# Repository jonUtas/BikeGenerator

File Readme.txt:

Pedal generator for open day. 

Based on Bafang bike motor.

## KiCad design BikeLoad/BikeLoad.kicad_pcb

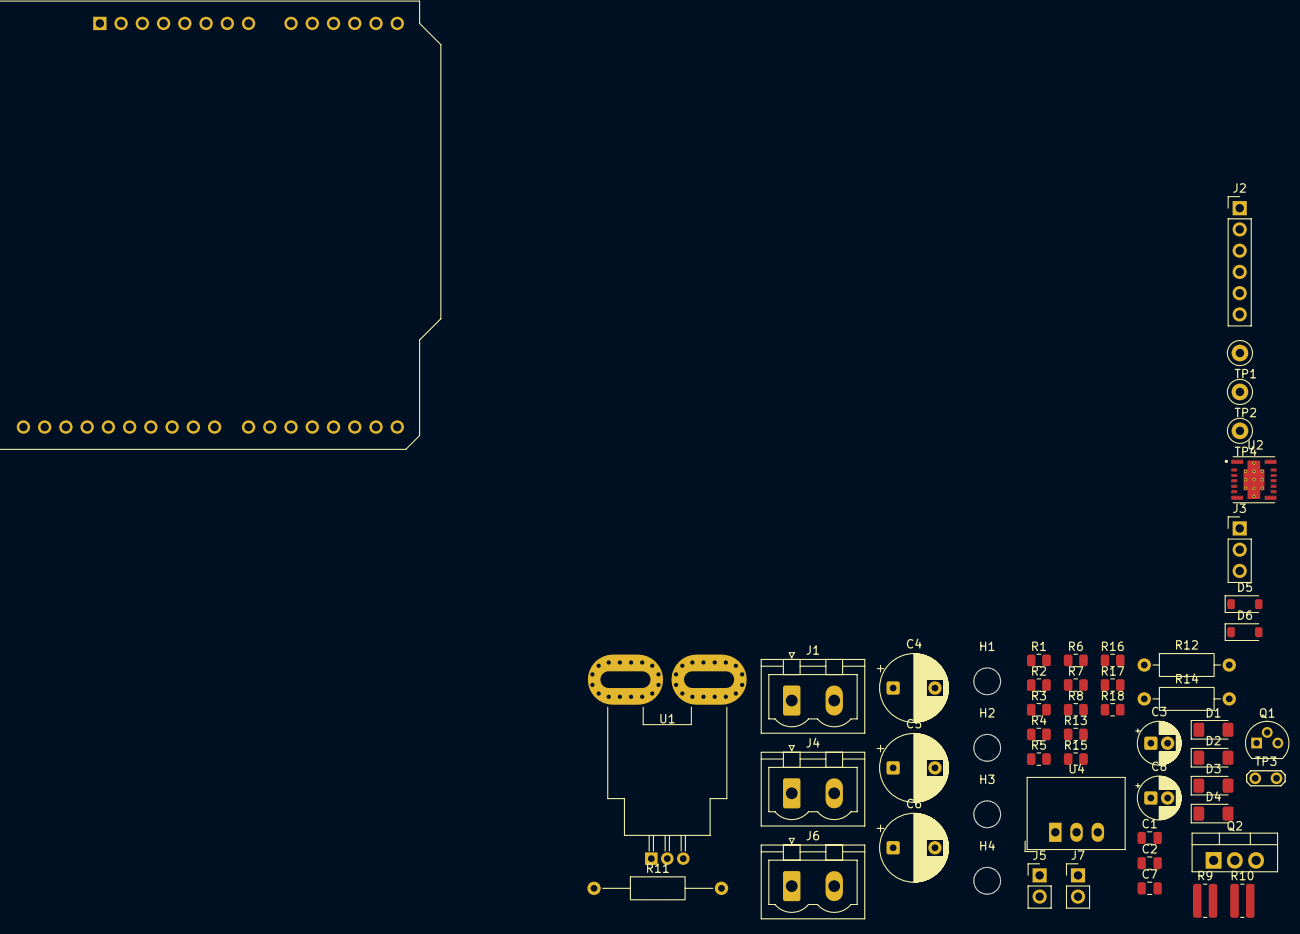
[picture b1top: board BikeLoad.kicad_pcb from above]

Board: 2 copper layers, 53 parts (0 on the bottom side), 26 nets, no tracks yet.

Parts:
A1: Arduino_UNO_R3
C1, C2, C7: C; C_0805_2012Metric
C3: C_Polarized; CP_Radial_D5.0mm_P2.00mm
C4, C5, C6: 1; CP_Radial_D8.0mm_P5.00mm
C8: 10u; CP_Radial_D5.0mm_P2.00mm
D1: BZV55B51; D_MiniMELF
D2, D3, D4: BZV55B4V3; D_MiniMELF
D5, D6: D; D_SOD-123
H1, H2, H3, H4: MountingHole; MountingHole_3.2mm_M3
J1: DC Input; PhoenixContact_MSTBVA_2,5_2-G-5,08_1x02_P5.08mm_Vertical
J2: Hall Input; PinHeader_1x06_P2.54mm_Vertical
J3: Pot Input; PinHeader_1x03_P2.54mm_Vertical
J4: Load; PhoenixContact_MSTBVA_2,5_2-G-5,08_1x02_P5.08mm_Vertical
J5: Temp sensor; PinHeader_1x02_P2.54mm_Vertical
J6: DC out; PhoenixContact_MSTBVA_2,5_2-G-5,08_1x02_P5.08mm_Vertical
J7: LoadControl; PinHeader_1x02_P2.54mm_Vertical
Q1: BC556; TO-92
Q2: PNP; TO-220-3_Vertical
R1, R5, R6, R15, R16, R17, R18: R; R_0805_2012Metric
R2, R3, R4, R7, R13: 10k; R_0805_2012Metric
R8: 1k; R_0805_2012Metric
R9, R10: R; R_0815_2038Metric
R11: R; R_Axial_DIN0207_L6.3mm_D2.5mm_P15.24mm_Horizontal
R12: R; R_Axial_DIN0207_L6.3mm_D2.5mm_P10.16mm_Horizontal
R14: 10k; R_Axial_DIN0207_L6.3mm_D2.5mm_P10.16mm_Horizontal
TP1, TP2, TP4: TestPoint; TestPoint_Loop_D1.80mm_Drill1.0mm_Beaded
TP3: TestPoint; TestPoint_2Pads_Pitch2.54mm_Drill0.8mm
U1: ACS770xCB-050U-PFF; Allegro_CB_PFF
U2: TPSM5601R5HRDAR; IC_TPSM5601R5HRDAR
U4: R-785.0-1.0; Converter_DCDC_RECOM_R-78E-0.5_THT

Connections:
+5V: A1.5 (+5V), J2.1, Q1.3 (E), R2.1, R3.1, R4.1, R7.1, R16.1, TP2.1, U1.1 (VCC), U4.3 (OUT)
+13V: D5.2 (A), J6.1, R5.1, R12.1, TP1.1, U2.7 (VOUT), U2.8 (VOUT__1)
/DC_metered: C2.1, C3.1, J4.1, Q2.3 (E), R13.2, U1.5 (IP-), U2.1 (VIN), U2.2 (EN), U2.14 (VIN__1)
/Hall_A: A1.19 (D4), J2.3, R2.2
/Hall_B: A1.20 (D5), J2.4, R3.2
/Hall_C: A1.21 (D6), J2.5, R4.2
/InputCurrent: A1.10 (A1), U1.3 (VIOUT)
/InputPot: A1.12 (A3), C1.1, R1.2
/InputVoltage: A1.9 (A0), R9.2, R10.1
/PWMout: A1.24 (D9), R15.1, R16.2
/SCapVolts: A1.13 (SDA/A4), R17.2, R18.1
/TempSensor: A1.11 (A2), C7.1, R8.2
GND: A1.6 (GND), A1.7 (GND), A1.29 (GND), C1.2, C2.2, C3.2, C6.2, C7.2, C8.2, D1.2 (A), D4.2 (A), J1.2, J2.2, J3.3, J4.2, J5.2, J6.2, J7.2, R6.2, R10.2, R11.2, R18.2, TP3.1, U1.2 (GND), U2.10 (AGND), U2.15 (PGND), U4.2 (GND)
unnamed: D1.1 (K), Q2.1 (B), R13.1
unnamed: C4.2, C5.1, D2.2 (A), D3.1 (K)
unnamed: C4.1, D2.1 (K), D6.2 (A), R12.2, R17.1, TP4.1
unnamed: C5.2, C6.1, D3.2 (A), D4.1 (K)
unnamed: D5.1 (K), D6.1 (K), U4.1 (IN)
unnamed: J1.1, R9.1, U1.4 (IP+)
unnamed: J3.2, R1.1
unnamed: J5.1, R7.2, R8.1
unnamed: C8.1, J7.1, R14.2
unnamed: Q1.2 (B), R15.2
unnamed: Q1.1 (C), R14.1
unnamed: Q2.2 (C), R11.1
unnamed: R5.2, R6.1, U2.9 (FB)

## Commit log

2025-07-22 builds debug but no screen
2025-07-22 runs ok
2025-07-23 this works, can update via ioc and touchgfx
2025-07-23 changed gauge
2025-07-23 pcb files
2025-07-23 with datasheets
2025-07-24 not working
2025-07-24 built from scratch again
2025-07-24 runs ok again
2025-07-24 added ADC pins
2025-07-24 added gpio pins
2025-07-24 working after pins added
2025-07-25 backlight disable test ok
2025-07-28 adc added, compiles and triggers interrupt
2025-07-30 interupt stops after a while
2025-07-30 schematic
2025-07-31 cant debug
2025-07-31 adc seems good
2025-07-31 readonly in linker script
2025-07-31 datasheets
2025-07-31 updating gauge works ok.
2025-08-01 gauge updates from pot
